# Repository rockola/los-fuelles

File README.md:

# los-fuelles
EQD Bellows clone for 1590A

* v0.1: initial import, unverified

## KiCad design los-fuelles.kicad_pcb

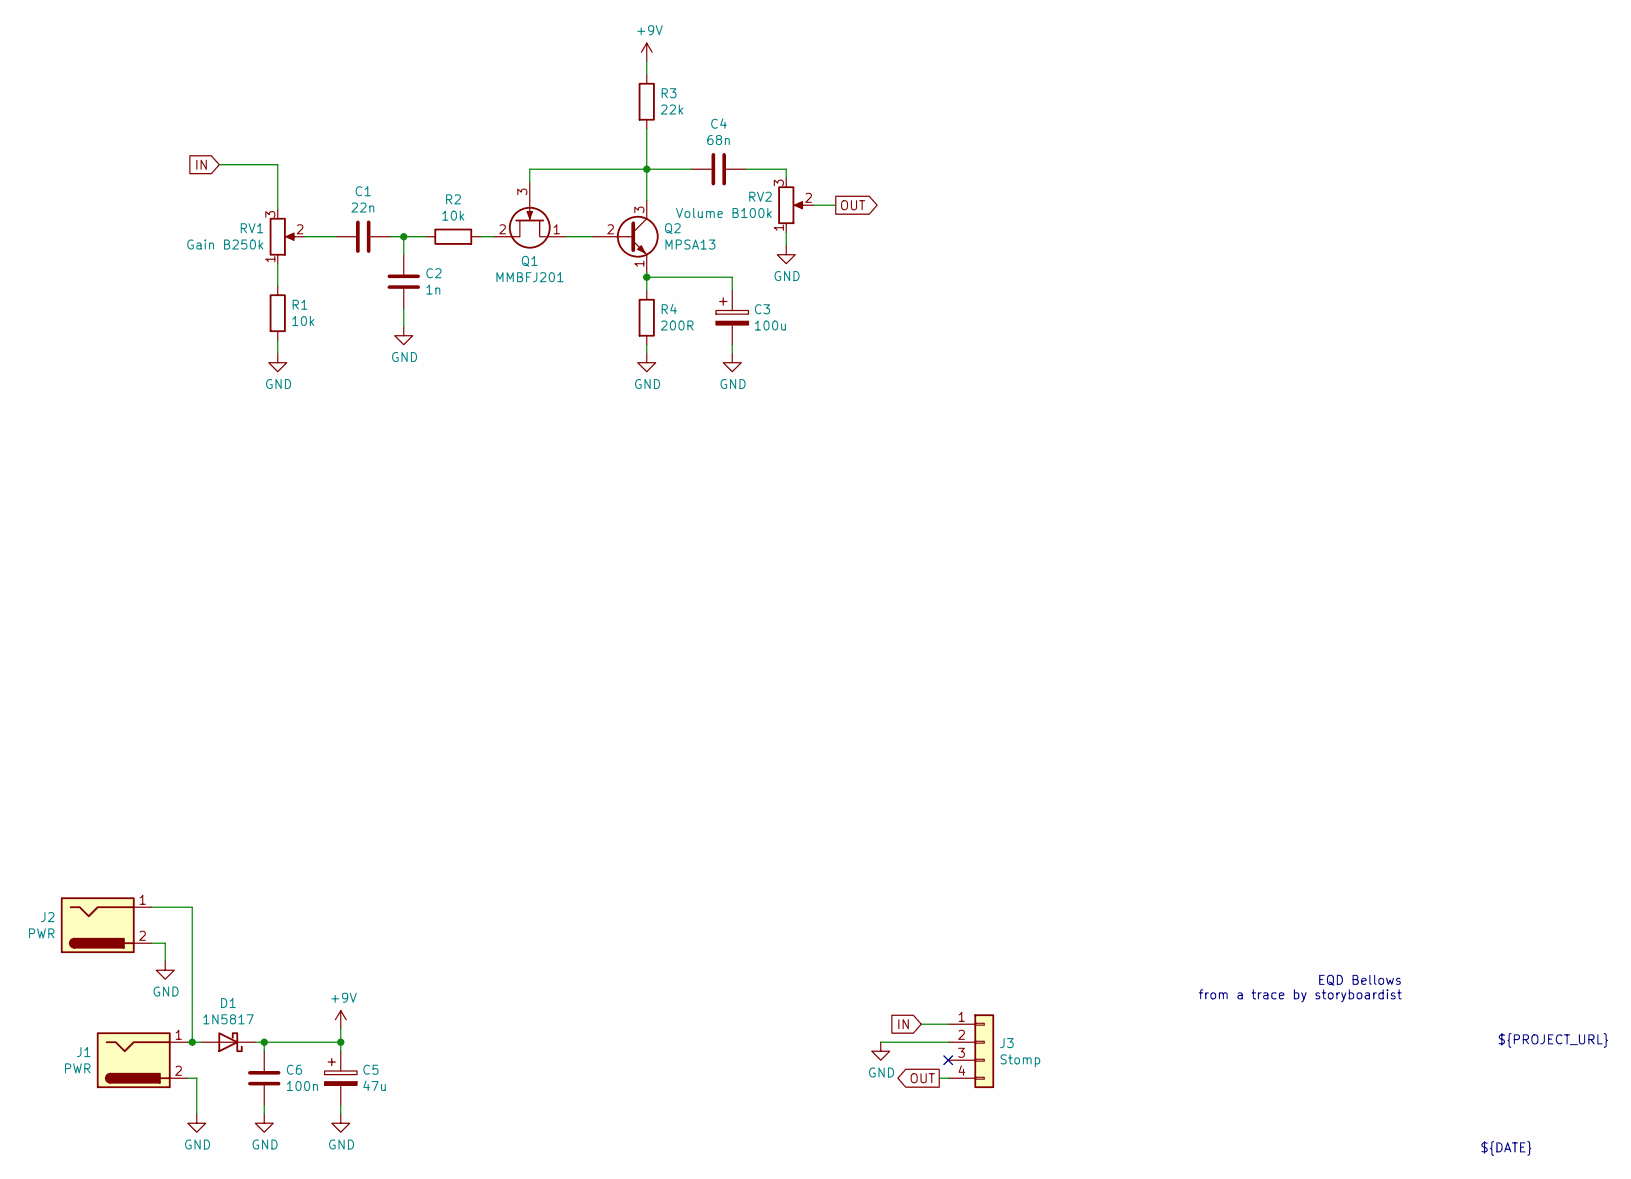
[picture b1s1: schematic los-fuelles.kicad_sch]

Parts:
C1: 22n; C_Box_7.2_2.5
C2: 1n; C_Box_7.2_2.5
C3: 100u; CP_D6.3_P2.50
C4: 68n; C_Box_7.2_2.5
C5: 47u; CP_D5.0_P2.50
C6: 100n; C_Box_7.2_2.5
D1: 1N5817; D_DO-41_SOD81_P10.16mm_Horizontal
J1: PWR; Power_Header_2pin
J2: PWR; Power_Header_2pin_TOP
J3: Stomp; Stomp_4pin
Q1: MMBFJ201; SOT-23
Q2: MPSA13; TO-92_Inline_Wide
R1, R2: 10k; R_DIN0207
R3: 22k; R_DIN0207
R4: 200R; R_DIN0207
RV1: Gain B250k; 9MM_METAL_SHAFT
RV2: Volume B100k; 9MM_METAL_SHAFT

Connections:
+9V: C5.1, C6.2, D1.1 (K), R3.1
GND: C2.2, C3.2, C5.2, C6.1, J1.2, J2.2, J3.2, R1.2, R4.2, RV2.1
IN: J3.1, RV1.3
unnamed: C1.1, RV1.2
unnamed: C1.2, C2.1, R2.1
unnamed: C3.1, Q2.1 (E), R4.1
unnamed: C4.1, Q1.3 (G), Q2.3 (C), R3.2
unnamed: C4.2, RV2.3
unnamed: D1.2 (A), J1.1, J2.1
unnamed: Q1.1 (D), Q2.2 (B)
unnamed: Q1.2 (S), R2.2
unnamed: R1.1, RV1.1
OUT: J3.4, RV2.2

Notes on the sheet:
${DATE}
EQD Bellows from a trace by storyboardist
${TITLE}
${REVISION}
${PROJECT_URL}

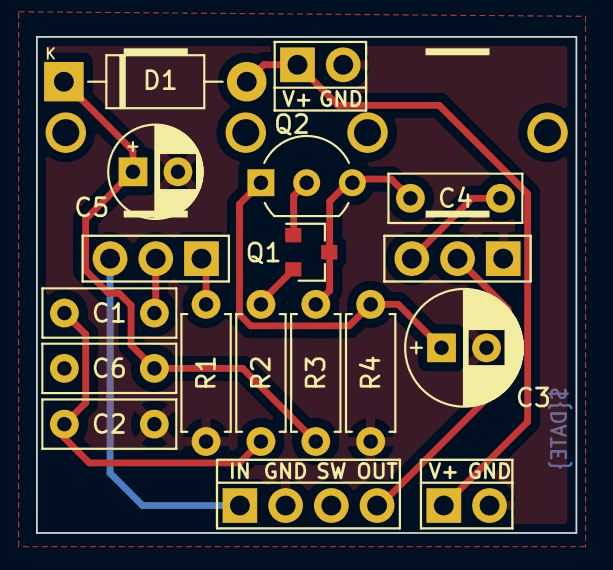
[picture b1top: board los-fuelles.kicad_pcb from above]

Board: 2 copper layers, 30.0 x 27.6 mm, 18 parts (0 on the bottom side), 13 nets.

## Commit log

2020-08-01 initial import
2020-08-01 initial README, preview images
2022-01-11 updated to KiCad 6.0
